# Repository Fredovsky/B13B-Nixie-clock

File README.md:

# B13B-Nixie-clock
Nixie clock made from F9057 Nixie tubes (B13B sockets).

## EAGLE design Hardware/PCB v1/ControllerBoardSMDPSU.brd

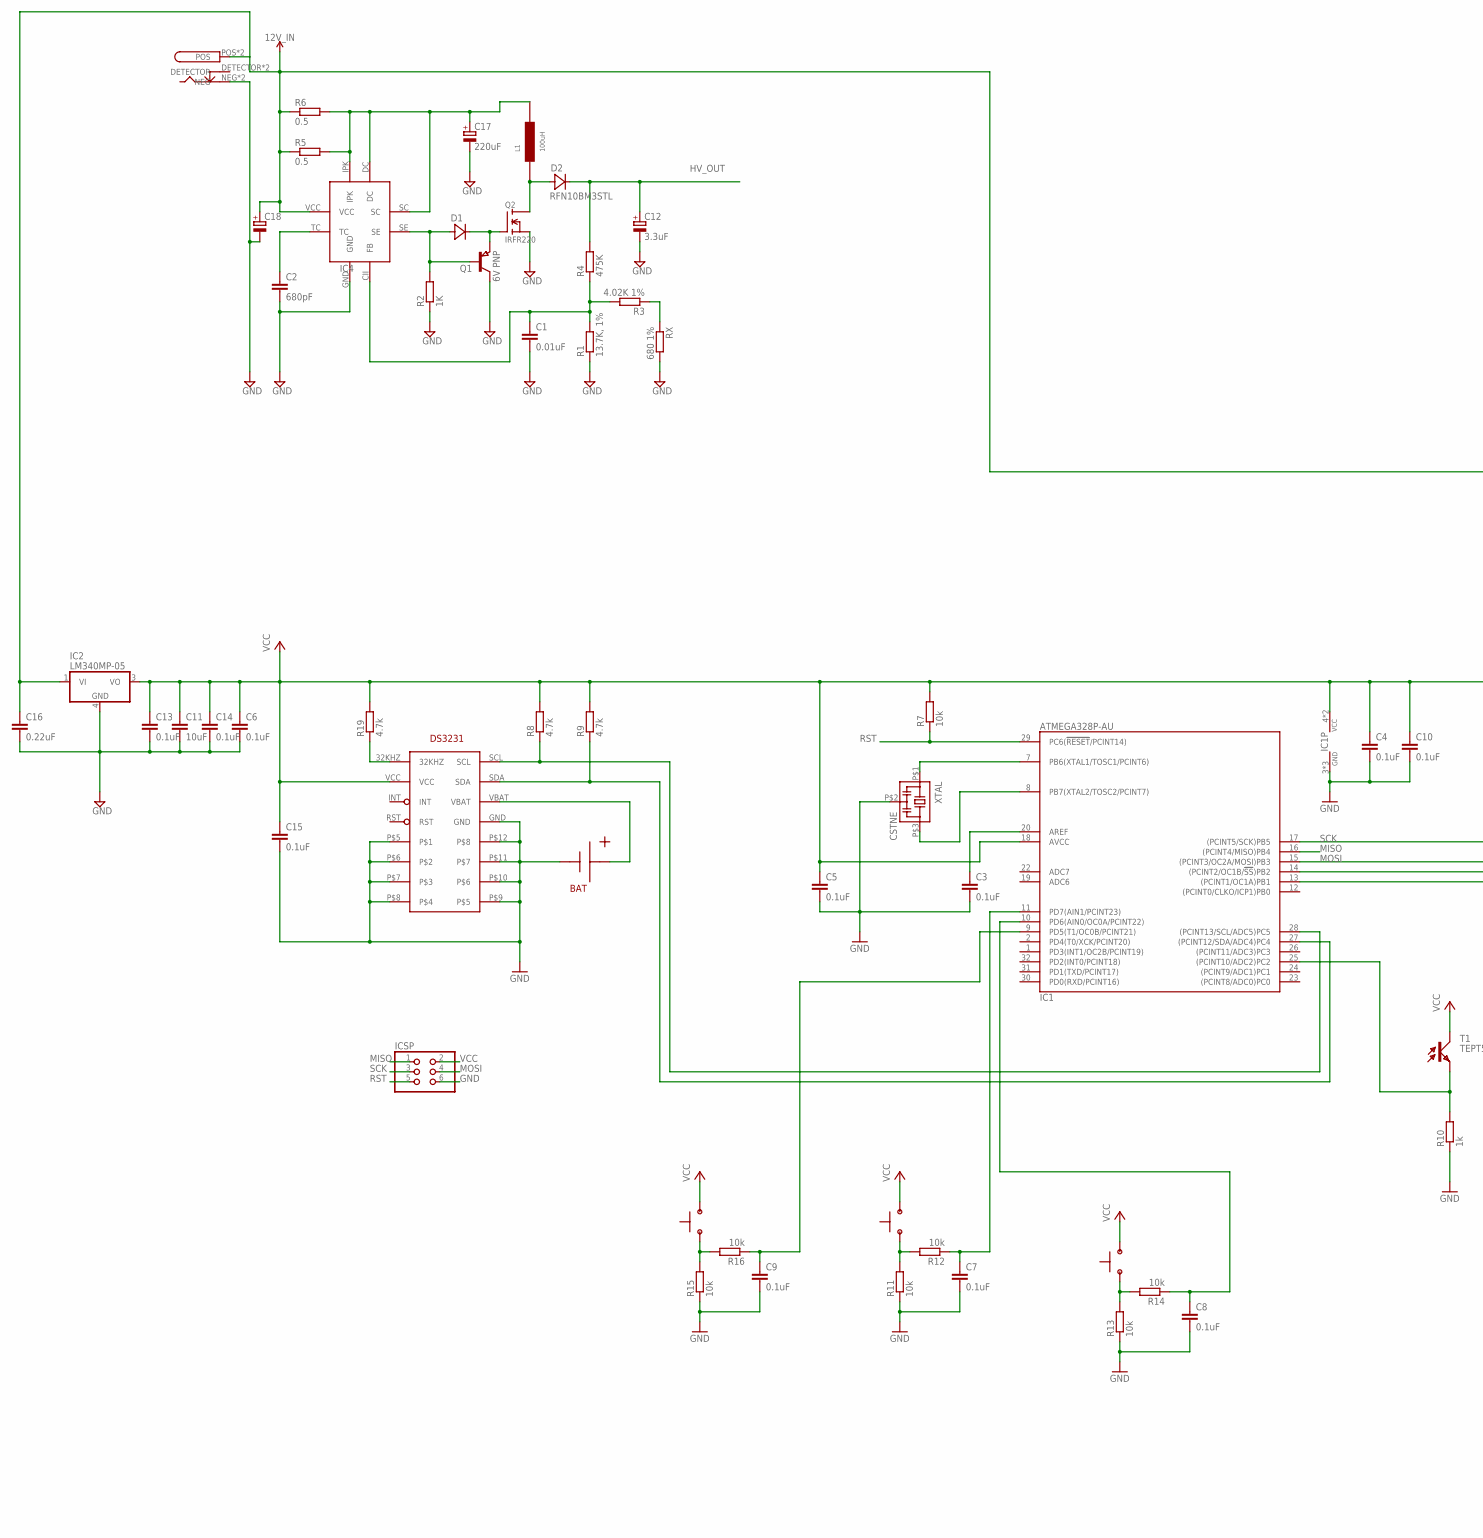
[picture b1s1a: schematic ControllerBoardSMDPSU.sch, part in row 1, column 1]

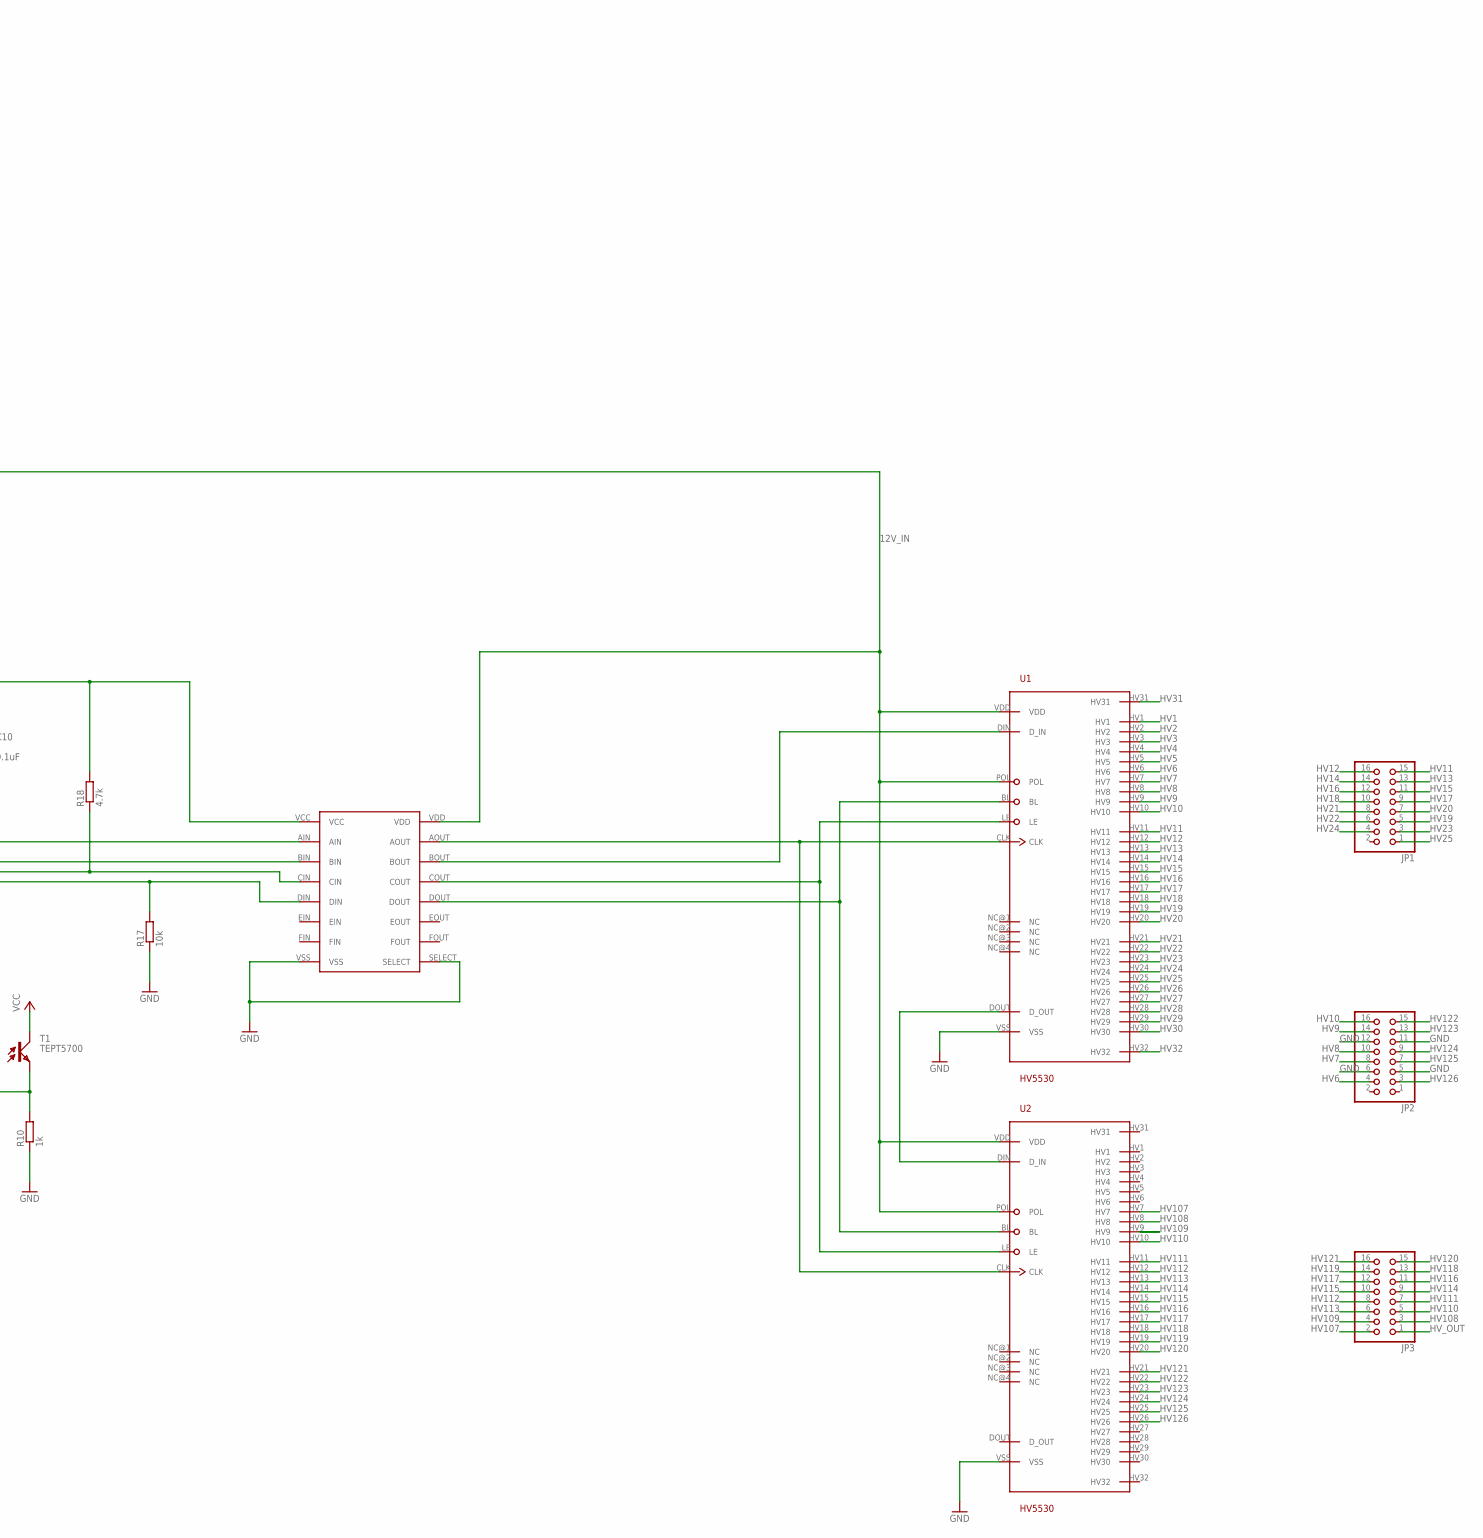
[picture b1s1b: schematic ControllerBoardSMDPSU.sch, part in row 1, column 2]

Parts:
12V: CUI_PWR_JACK
BAT: CR2032-SMD-HLDR; CR2032-SMD
C1: 0.01uF; C0603
C2: 680pF; C0603
C3, C4, C5, C6, C7, C8, C9, C10, C13, C14, C15: 0.1uF; C0603
C11: 10uF; C0603
C12: 3.3uF; 153CLV-0810
C16: 0.22uF; C0603
C17: 220uF; 153CLV-0605
C18: CPOL-EU153CLV-0605; 153CLV-0605
D1: SOT123DIODE; SOD123
D2: RFN10BM3STL; TO252
IC1: ATMEGA328P-AU; QFP32_7X7_0.80
IC2: LM340MP-05; SOT223
IC3: CD4504BTSSOP16; SOP65P640X120-16N
IC4: MC34063; SOIC127P600X175-8
ICSP: PINHD-2X3; 2X03
JP1, JP2, JP3: PINHD-2X8; 2X08
L1: 100uH; SDR1105
Q1: 6V PNP; SOT23
Q2: IRFR220; DPAK
R1: 13.7K, 1%; R1206
R2: 1K; R1206
R3: 4.02K 1%; R1206
R4: 475K; R1206
R5, R6: 0.5; R1206
R7, R11, R12, R13, R14, R15, R16, R17: 10k; R0603
R8, R9, R18, R19: 4.7k; R0603
R10: 1k; R0603
RTC: DS3231-CORRECT; SOIC16-CORRECT
RX: 680 1%; R1206
S1, S2, S3: TL1105
T1: TEPT5700; BPX81
U1, U2: HV5530; 44_PQFP_CORRECTED
XTAL: CSTNE

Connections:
12V_IN: 12V.POS, 12V.POS1 (POS), C16.1, C18.+, IC2.1 (VI), IC3.VDD, IC4.VCC, R5.1, R6.1, U1.POL, U1.VDD, U2.POL, U2.VDD
GND: 12V.NEG, 12V.NEG1 (NEG), BAT.NEG, C1.2, C2.2, C3.2, C4.2, C5.2, C6.2, C7.2, C8.2, C9.2, C10.2, C11.2, C12.-, C13.2, C14.2, C15.2, C16.2, C17.-, C18.-, IC1.3 (GND), IC1.5 (GND), IC1.21 (GND), IC2.4 (GND), IC3.SELECT, IC3.VSS, IC4.GND, ICSP.6, JP2.5, JP2.6, JP2.11, JP2.12, Q1.3 (C), Q2.3 (S), R1.1, R2.1, R10.1, R11.1, R13.1, R15.1, R17.1, RTC.GND, RTC.P$5, RTC.P$6, RTC.P$7, RTC.P$8, RTC.P$9, RTC.P$10, RTC.P$11, RTC.P$12, RX.2, U1.VSS, U2.VSS, XTAL.P$2 (2)
HV1: U1.HV1
HV2: U1.HV2
HV3: U1.HV3
HV4: U1.HV4
HV5: U1.HV5
HV6: JP2.4, U1.HV6
HV7: JP2.8, U1.HV7
HV8: JP2.10, U1.HV8
HV9: JP2.14, U1.HV9
HV10: JP2.16, U1.HV10
HV11: JP1.15, U1.HV11
HV12: JP1.16, U1.HV12
HV13: JP1.13, U1.HV13
HV14: JP1.14, U1.HV14
HV15: JP1.11, U1.HV15
HV16: JP1.12, U1.HV16
HV17: JP1.9, U1.HV17
HV18: JP1.10, U1.HV18
HV19: JP1.5, U1.HV19
HV20: JP1.7, U1.HV20
HV21: JP1.8, U1.HV21
HV22: JP1.6, U1.HV22
HV23: JP1.3, U1.HV23
HV24: JP1.4, U1.HV24
HV25: JP1.1, U1.HV25
HV26: U1.HV26
HV27: U1.HV27
HV28: U1.HV28
HV29: U1.HV29
HV30: U1.HV30
HV31: U1.HV31
HV32: U1.HV32
HV107: JP3.2, U2.HV7
HV108: JP3.3, U2.HV8
HV109: JP3.4, U2.HV9
HV110: JP3.5, U2.HV10
HV111: JP3.7, U2.HV11
HV112: JP3.8, U2.HV12
HV113: JP3.6, U2.HV13
HV114: JP3.9, U2.HV14
HV115: JP3.10, U2.HV15
HV116: JP3.11, U2.HV16
HV117: JP3.12, U2.HV17
HV118: JP3.13, U2.HV18
HV119: JP3.14, U2.HV19
HV120: JP3.15, U2.HV20
HV121: JP3.16, U2.HV21
HV122: JP2.15, U2.HV22
HV123: JP2.13, U2.HV23
HV124: JP2.9, U2.HV24
HV125: JP2.7, U2.HV25
HV126: JP2.3, U2.HV26
HV_OUT: C12.+, D2.3 (C), JP3.1, R4.2
MISO: IC1.16 ((PCINT4/MISO)PB4), ICSP.1
MOSI: IC1.15 ((PCINT3/OC2A/MOSI)PB3), IC3.BIN, ICSP.4
unnamed: BAT.POS@1 (POS), BAT.POS@2 (POS), RTC.VBAT
unnamed: IC1.7 (PB6(XTAL1/TOSC1/PCINT6)), XTAL.P$1 (1)
unnamed: IC1.8 (PB7(XTAL2/TOSC2/PCINT7)), XTAL.P$3 (3)
unnamed: R19.1, RTC.32KHZ
unnamed: IC3.AOUT, U1.CLK, U2.CLK
unnamed: U1.DOUT (D_OUT), U2.DIN (D_IN)
unnamed: IC3.BOUT, U1.DIN (D_IN)
unnamed: C17.+, IC4.DC, IC4.IPK, IC4.SC, L1.P$2, R5.2, R6.2
unnamed: C2.1, IC4.TC
unnamed: D1.2 (A), IC4.SE, Q1.1 (B), R2.2
unnamed: D1.1 (C), Q1.2 (E), Q2.1 (G)
unnamed: D2.1 (A), D2.2 (A), L1.P$1, Q2.2 (D)
unnamed: C1.1, IC4.CII (FB), R1.2, R3.2, R4.1
unnamed: IC1.14 ((PCINT2/OC1B/!SS!)PB2), IC3.CIN, R18.1
unnamed: IC1.13 ((PCINT1/OC1A)PB1), IC3.DIN, R17.2
unnamed: IC3.COUT, U1.LE, U2.LE
unnamed: IC3.DOUT, U1.BL, U2.BL
unnamed: C3.1, IC1.20 (AREF)
unnamed: IC1.25 ((PCINT10/ADC2)PC2), R10.2, T1.E
unnamed: R3.1, RX.1
unnamed: R13.2, R14.2, S2.1, S2.2
unnamed: R11.2, R12.2, S1.1, S1.2
unnamed: C8.1, IC1.10 (PD6(AIN0/OC0A/PCINT22)), R14.1
unnamed: C7.1, IC1.11 (PD7(AIN1/PCINT23)), R12.1
unnamed: R15.2, R16.2, S3.1, S3.2
unnamed: C9.1, IC1.9 (PD5(T1/OC0B/PCINT21)), R16.1
RST: IC1.29 (PC6(!RESET!/PCINT14)), ICSP.5, R7.1
SCK: IC1.17 ((PCINT5/SCK)PB5), IC3.AIN, ICSP.3
SCL: IC1.28 ((PCINT13/SCL/ADC5)PC5), R8.1, RTC.SCL
SDA: IC1.27 ((PCINT12/SDA/ADC4)PC4), R9.1, RTC.SDA
VCC: C4.1, C5.1, C6.1, C10.1, C11.1, C13.1, C14.1, C15.1, IC1.4 (VCC), IC1.6 (VCC), IC1.18 (AVCC), IC2.3 (VO), IC3.VCC, ICSP.2, R7.2, R8.2, R9.2, R18.2, R19.2, RTC.VCC, S1.3, S1.4, S2.3, S2.4, S3.3, S3.4, T1.C

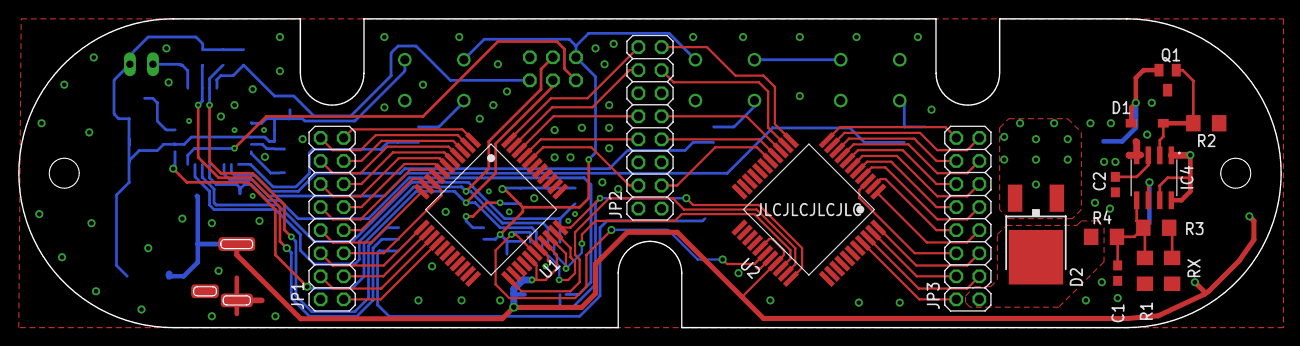
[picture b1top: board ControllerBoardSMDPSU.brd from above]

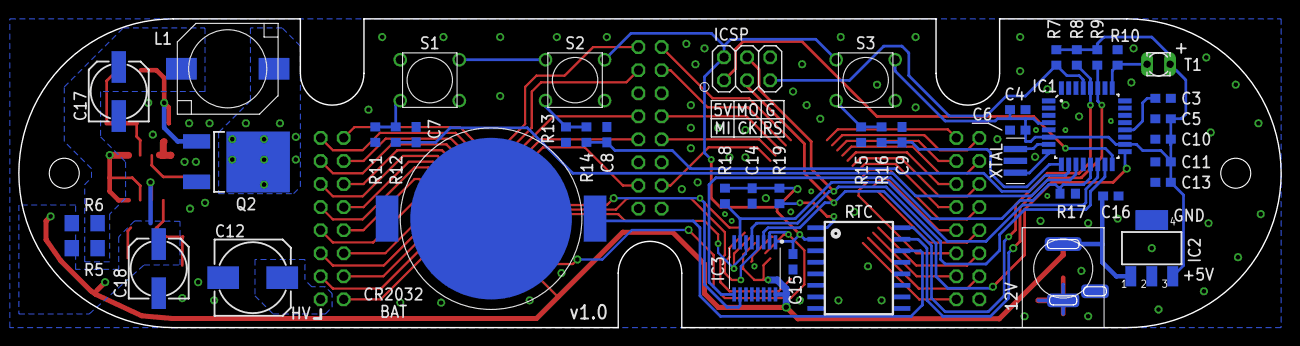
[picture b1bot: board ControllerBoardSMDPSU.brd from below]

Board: 2 copper layers, 139.0 x 34.0 mm, 61 parts (45 on the bottom side), 76 nets.

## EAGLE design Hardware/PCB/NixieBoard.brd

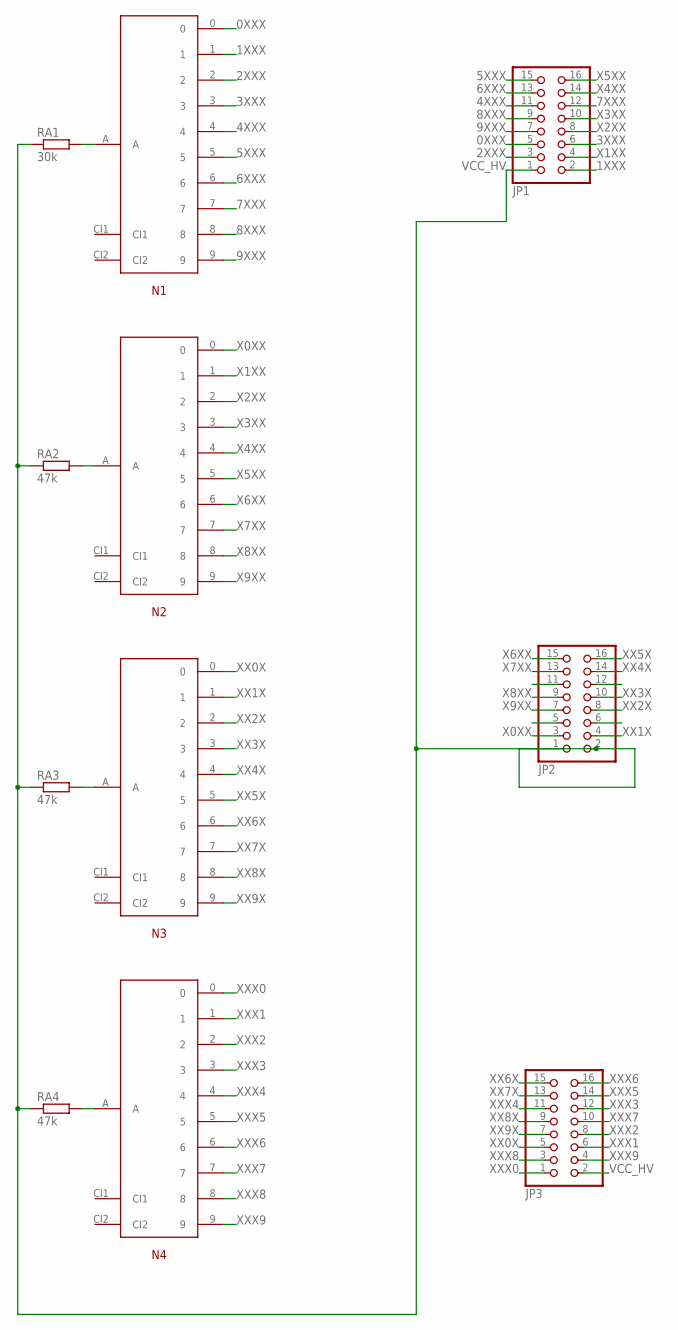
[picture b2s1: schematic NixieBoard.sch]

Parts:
JP1, JP2, JP3: PINHD-2X8; 2X08
N1, N2, N3, N4: F9057TUBE; F9057PIN
RA1: 30k; R2010
RA2, RA3, RA4: 47k; R2010

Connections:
0XXX: JP1.5, N1.0
1XXX: JP1.2, N1.1
2XXX: JP1.3, N1.2
3XXX: JP1.6, N1.3
4XXX: JP1.11, N1.4
5XXX: JP1.15, N1.5
6XXX: JP1.13, N1.6
7XXX: JP1.12, N1.7
8XXX: JP1.9, N1.8
9XXX: JP1.7, N1.9
unnamed: N4.A, RA4.2
unnamed: N3.A, RA3.2
unnamed: N2.A, RA2.2
unnamed: N1.A, RA1.2
VCC_HV: JP1.1, JP2.1, JP2.2, JP3.2, RA1.1, RA2.1, RA3.1, RA4.1
X0XX: JP2.3, N2.0
X1XX: JP1.4, N2.1
X2XX: JP1.8, N2.2
X3XX: JP1.10, N2.3
X4XX: JP1.14, N2.4
X5XX: JP1.16, N2.5
X6XX: JP2.15, N2.6
X7XX: JP2.13, N2.7
X8XX: JP2.9, N2.8
X9XX: JP2.7, N2.9
XX0X: JP3.5, N3.0
XX1X: JP2.4, N3.1
XX2X: JP2.8, N3.2
XX3X: JP2.10, N3.3
XX4X: JP2.14, N3.4
XX5X: JP2.16, N3.5
XX6X: JP3.15, N3.6
XX7X: JP3.13, N3.7
XX8X: JP3.9, N3.8
XX9X: JP3.7, N3.9
XXX0: JP3.1, N4.0
XXX1: JP3.6, N4.1
XXX2: JP3.8, N4.2
XXX3: JP3.12, N4.3
XXX4: JP3.11, N4.4
XXX5: JP3.14, N4.5
XXX6: JP3.16, N4.6
XXX7: JP3.10, N4.7
XXX8: JP3.3, N4.8
XXX9: JP3.4, N4.9

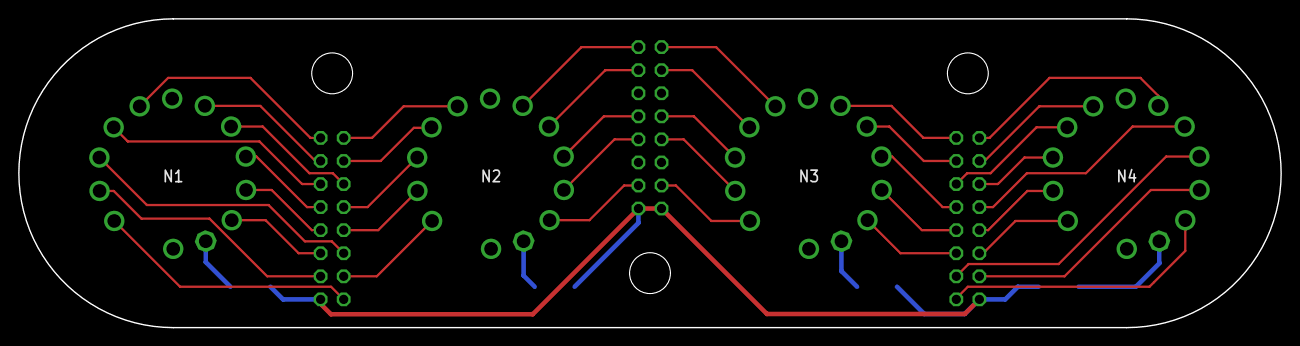
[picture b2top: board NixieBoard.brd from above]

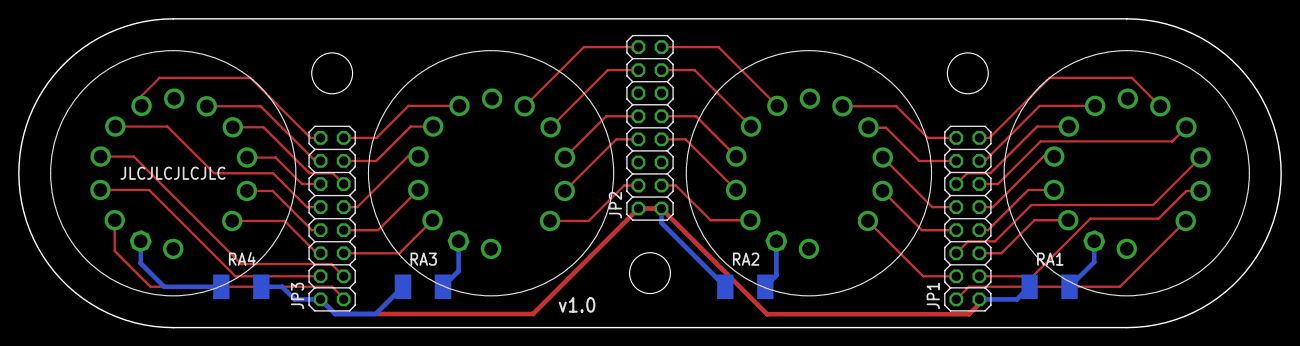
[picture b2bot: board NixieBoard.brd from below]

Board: 2 copper layers, 139.0 x 34.0 mm, 11 parts (7 on the bottom side), 45 nets.

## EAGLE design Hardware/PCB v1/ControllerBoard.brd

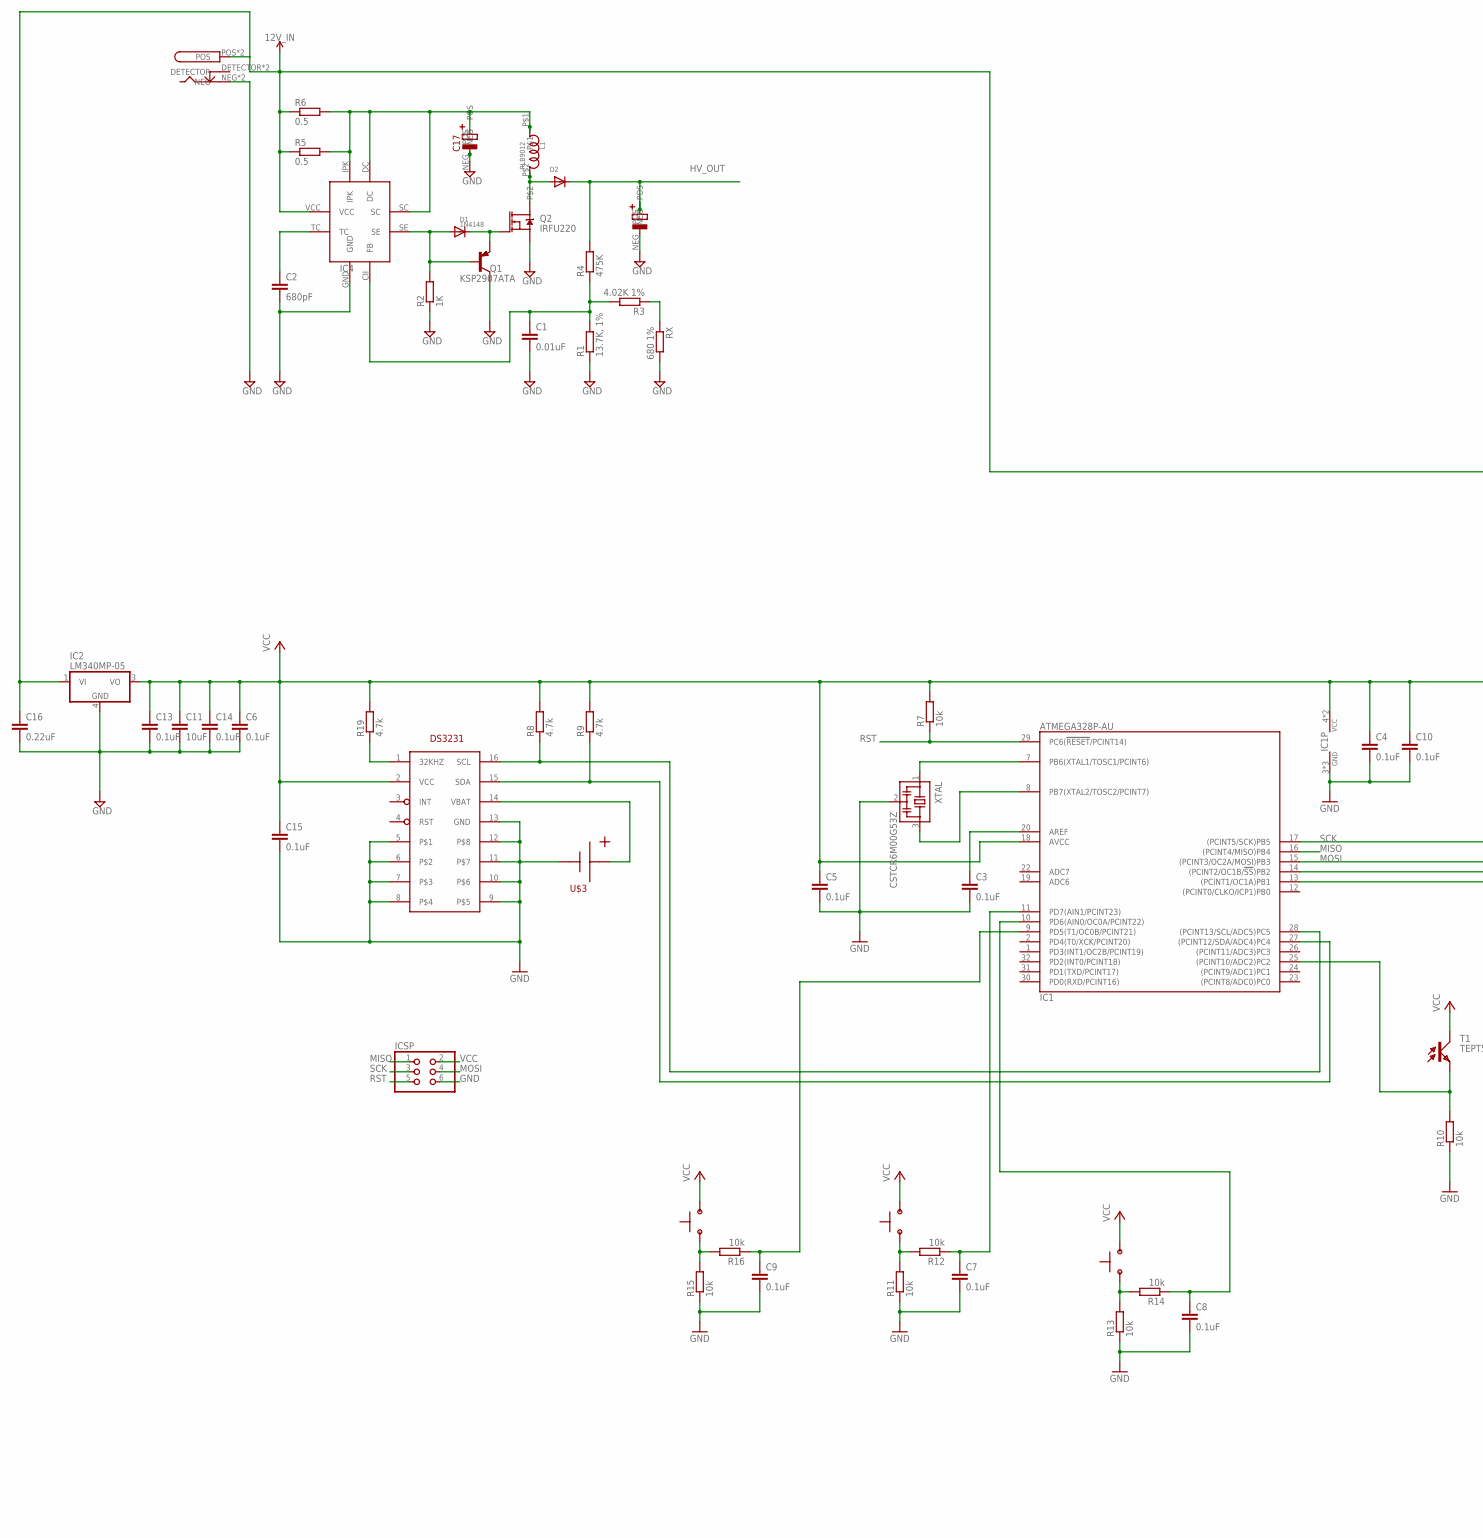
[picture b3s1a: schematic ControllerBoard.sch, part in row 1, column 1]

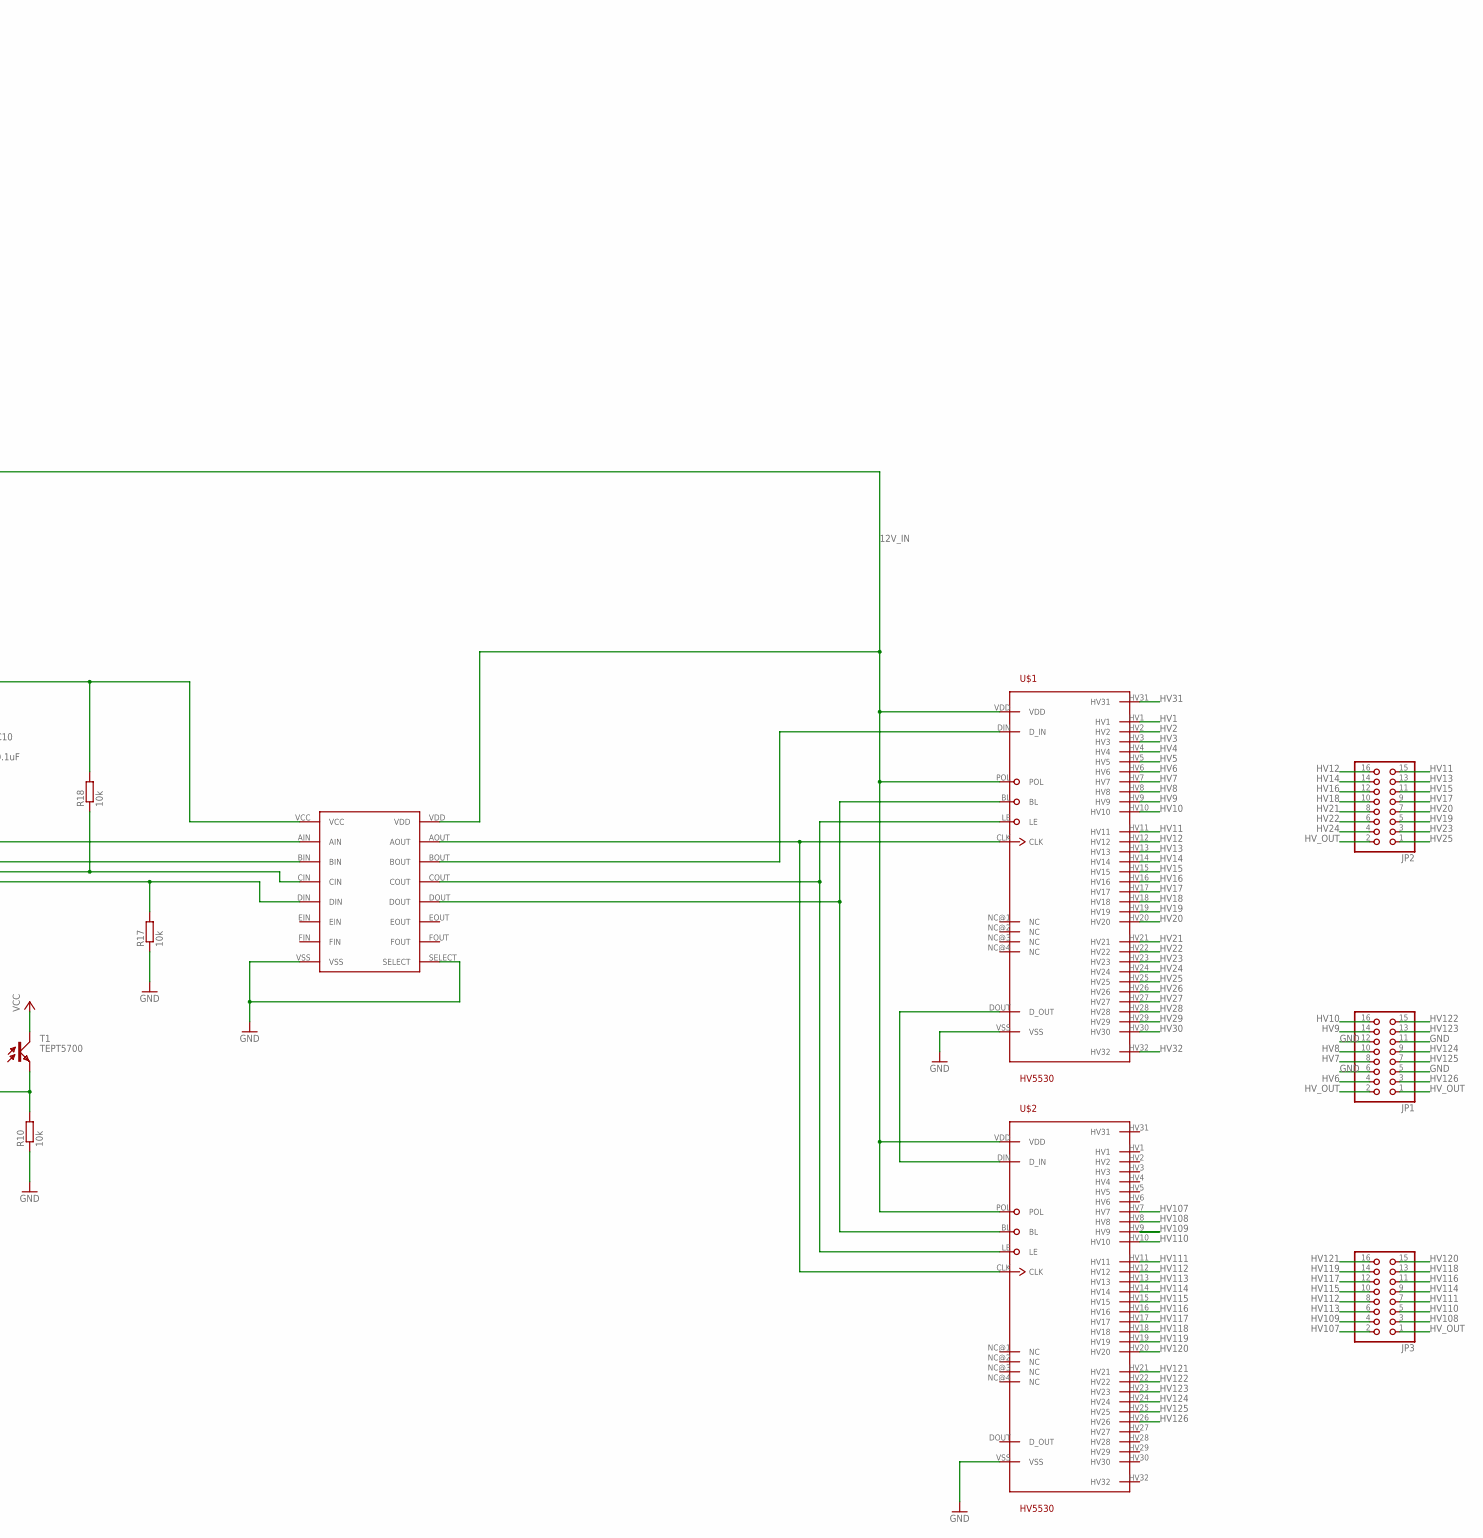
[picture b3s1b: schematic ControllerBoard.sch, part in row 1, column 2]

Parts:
12V: CUI_PWR_JACK
C1: 0.01uF; C0603
C2: 680pF; C0603
C3, C4, C5, C6, C7, C8, C9, C10, C13, C14, C15: 0.1uF; C0603
C11: 10uF; C0603
C12: ECA-2DM3R3
C16: 0.22uF; C0603
C17: EEU-FM1
D1: 1N4148; SOD-123
D2: DIODESOD-123; SOD-123
IC1: ATMEGA328P-AU; QFP32_7X7_0.80
IC2: LM340MP-05; SOT223
IC3: CD4504BTSSOP16; SOP65P640X120-16N
IC4: MC34063; SOIC127P600X175-8
ICSP: PINHD-2X3; 2X03
JP1, JP2, JP3: PINHD-2X8; 2X08
L1: RLB9012
Q1: KSP2907ATA; TO92-EBC-OVAL
Q2: IRFU220; TO220V
R1: 13.7K, 1%; R1206
R2: 1K; R1206
R3: 4.02K 1%; R1206
R4: 475K; R1206
R5, R6: 0.5; R1206
R7, R10, R11, R12, R13, R14, R15, R16, R17, R18: 10k; R0603
R8, R9, R19: 4.7k; R0603
RTC: DS3231; SO16
RX: 680 1%; R1206
S1, S2, S3: TL1105
T1: TEPT5700; BPX81
U$1, U$2: HV5530; 44_PQFP_CORRECTED
U$3: CR2032-SMD-HLDR; CR2032-SMD
XTAL: CSTCR6M00G53Z; CSTCR6M

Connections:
12V_IN: 12V.POS, 12V.POS1 (POS), C16.1, IC2.1 (VI), IC3.VDD, IC4.VCC, R5.1, R6.1, U$1.POL, U$1.VDD, U$2.POL, U$2.VDD
GND: 12V.NEG, 12V.NEG1 (NEG), C1.2, C2.2, C3.2, C4.2, C5.2, C6.2, C7.2, C8.2, C9.2, C10.2, C11.2, C12.NEG, C13.2, C14.2, C15.2, C16.2, C17.NEG, IC1.3 (GND), IC1.5 (GND), IC1.21 (GND), IC2.4 (GND), IC3.SELECT, IC3.VSS, IC4.GND, ICSP.6, JP1.5, JP1.6, JP1.11, JP1.12, Q1.C, Q2.3 (S), R1.1, R2.1, R10.1, R11.1, R13.1, R15.1, R17.1, RTC.5, RTC.6, RTC.7, RTC.8, RTC.9, RTC.10, RTC.11, RTC.12, RTC.13 (GND), RX.2, U$1.VSS, U$2.VSS, U$3.NEG, XTAL.2
HV1: U$1.HV1
HV2: U$1.HV2
HV3: U$1.HV3
HV4: U$1.HV4
HV5: U$1.HV5
HV6: JP1.4, U$1.HV6
HV7: JP1.8, U$1.HV7
HV8: JP1.10, U$1.HV8
HV9: JP1.14, U$1.HV9
HV10: JP1.16, U$1.HV10
HV11: JP2.15, U$1.HV11
HV12: JP2.16, U$1.HV12
HV13: JP2.13, U$1.HV13
HV14: JP2.14, U$1.HV14
HV15: JP2.11, U$1.HV15
HV16: JP2.12, U$1.HV16
HV17: JP2.9, U$1.HV17
HV18: JP2.10, U$1.HV18
HV19: JP2.5, U$1.HV19
HV20: JP2.7, U$1.HV20
HV21: JP2.8, U$1.HV21
HV22: JP2.6, U$1.HV22
HV23: JP2.3, U$1.HV23
HV24: JP2.4, U$1.HV24
HV25: JP2.1, U$1.HV25
HV26: U$1.HV26
HV27: U$1.HV27
HV28: U$1.HV28
HV29: U$1.HV29
HV30: U$1.HV30
HV31: U$1.HV31
HV32: U$1.HV32
HV107: JP3.2, U$2.HV7
HV108: JP3.3, U$2.HV8
HV109: JP3.4, U$2.HV9
HV110: JP3.5, U$2.HV10
HV111: JP3.7, U$2.HV11
HV112: JP3.8, U$2.HV12
HV113: JP3.6, U$2.HV13
HV114: JP3.9, U$2.HV14
HV115: JP3.10, U$2.HV15
HV116: JP3.11, U$2.HV16
HV117: JP3.12, U$2.HV17
HV118: JP3.13, U$2.HV18
HV119: JP3.14, U$2.HV19
HV120: JP3.15, U$2.HV20
HV121: JP3.16, U$2.HV21
HV122: JP1.15, U$2.HV22
HV123: JP1.13, U$2.HV23
HV124: JP1.9, U$2.HV24
HV125: JP1.7, U$2.HV25
HV126: JP1.3, U$2.HV26
HV_OUT: C12.POS, D2.C, JP1.1, JP1.2, JP2.2, JP3.1, R4.2
MISO: IC1.16 ((PCINT4/MISO)PB4), ICSP.1
MOSI: IC1.15 ((PCINT3/OC2A/MOSI)PB3), IC3.BIN, ICSP.4
unnamed: RTC.14 (VBAT), U$3.POS@1 (POS), U$3.POS@2 (POS)
unnamed: IC1.7 (PB6(XTAL1/TOSC1/PCINT6)), XTAL.1
unnamed: IC1.8 (PB7(XTAL2/TOSC2/PCINT7)), XTAL.3
unnamed: R19.1, RTC.1 (32KHZ)
unnamed: IC3.AOUT, U$1.CLK, U$2.CLK
unnamed: U$1.DOUT (D_OUT), U$2.DIN (D_IN)
unnamed: IC3.BOUT, U$1.DIN (D_IN)
unnamed: C17.POS, IC4.DC, IC4.IPK, IC4.SC, L1.P$1, R5.2, R6.2
unnamed: C2.1, IC4.TC
unnamed: D1.A, IC4.SE, Q1.B, R2.2
unnamed: D1.C, Q1.E, Q2.1 (G)
unnamed: D2.A, L1.P$2, Q2.2 (D)
unnamed: C1.1, IC4.CII (FB), R1.2, R3.2, R4.1
unnamed: IC1.14 ((PCINT2/OC1B/!SS!)PB2), IC3.CIN, R18.1
unnamed: IC1.13 ((PCINT1/OC1A)PB1), IC3.DIN, R17.2
unnamed: IC3.COUT, U$1.LE, U$2.LE
unnamed: IC3.DOUT, U$1.BL, U$2.BL
unnamed: C3.1, IC1.20 (AREF)
unnamed: IC1.25 ((PCINT10/ADC2)PC2), R10.2, T1.E
unnamed: R3.1, RX.1
unnamed: R13.2, R14.2, S2.1, S2.2
unnamed: R11.2, R12.2, S1.1, S1.2
unnamed: C8.1, IC1.10 (PD6(AIN0/OC0A/PCINT22)), R14.1
unnamed: C7.1, IC1.11 (PD7(AIN1/PCINT23)), R12.1
unnamed: R15.2, R16.2, S3.1, S3.2
unnamed: C9.1, IC1.9 (PD5(T1/OC0B/PCINT21)), R16.1
RST: IC1.29 (PC6(!RESET!/PCINT14)), ICSP.5, R7.1
SCK: IC1.17 ((PCINT5/SCK)PB5), IC3.AIN, ICSP.3
SCL: IC1.28 ((PCINT13/SCL/ADC5)PC5), R8.1, RTC.16 (SCL)
SDA: IC1.27 ((PCINT12/SDA/ADC4)PC4), R9.1, RTC.15 (SDA)
VCC: C4.1, C5.1, C6.1, C10.1, C11.1, C13.1, C14.1, C15.1, IC1.4 (VCC), IC1.6 (VCC), IC1.18 (AVCC), IC2.3 (VO), IC3.VCC, ICSP.2, R7.2, R8.2, R9.2, R18.2, R19.2, RTC.2 (VCC), S1.3, S1.4, S2.3, S2.4, S3.3, S3.4, T1.C

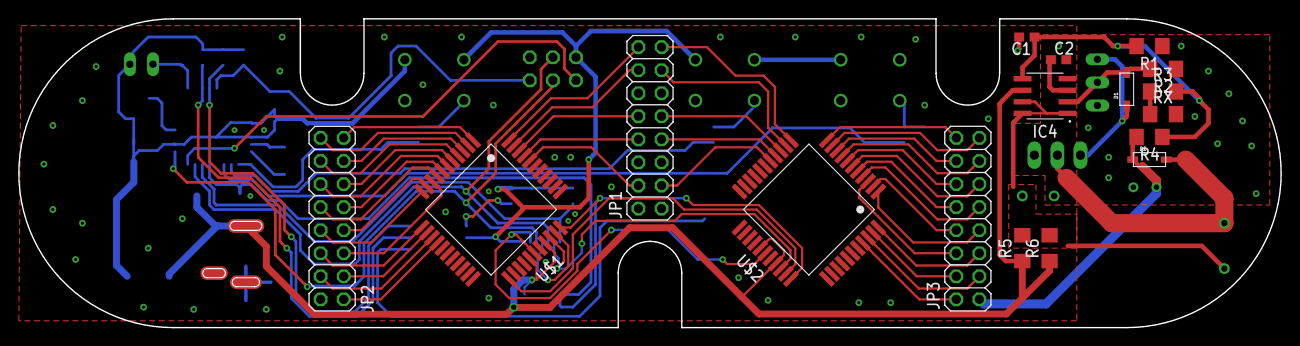
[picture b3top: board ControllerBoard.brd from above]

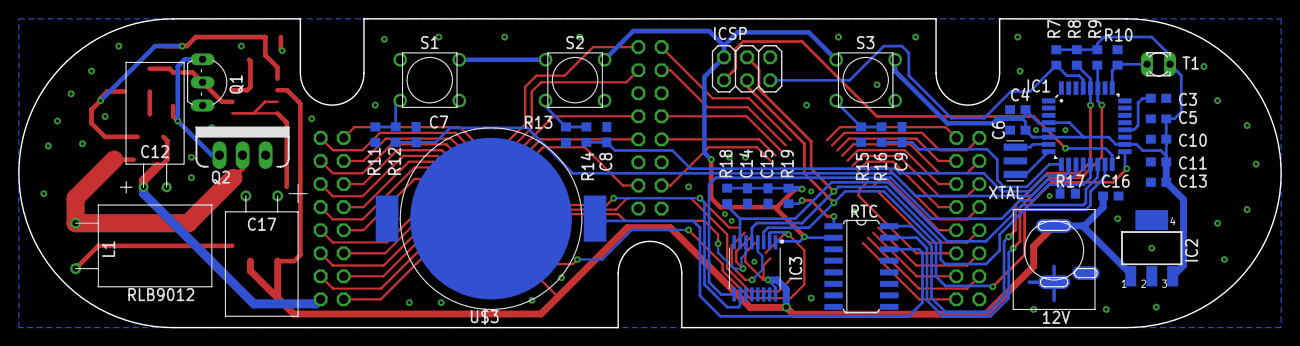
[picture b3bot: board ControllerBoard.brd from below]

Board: 2 copper layers, 139.0 x 34.0 mm, 60 parts (43 on the bottom side), 76 nets.

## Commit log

2021-03-23 Project creation
    Added all project files.
2021-03-23 Reorganized files and added PCB BOM.
    Bill of materials added for V1 of the clock PCB using SMD for PSU.
2021-12-12 First flash CPU clock bug fix
    RTCLib version added and CPU clock speed protocol for first upload.
2021-12-23 Update main.cpp
    Long Cathode Poisoning Prevention Routine set for 30min at 3am, short routine every hour for 15 seconds.
2025-10-16 Added v1.1
    v1.1 = modified Control board and back board for simpler 2-buttons set up (no more date/year functionnality as it was useless).
    PCBs now all on KiCAD.
    Added an updated BOM and 3D Print files if unable to make wooden case.
2025-12-12 Set CPU frequency to 16MHz and configure fuses
    Updated CPU frequency to 16MHz and added fuse settings for external crystal.
2025-12-12 Add temporary file to Software directory
2025-12-12 Update README for Nixie Clock v1.1 changes
    V1.1 update removes a push button and light sensor, changes back button functions, and adjusts brightness automatically.
2025-12-12 Update README for Nixie Clock v1.1 features and changes
    Version 1.1 introduces a simplified interface and improved features, including automatic brightness adjustment and error handling.
2025-12-12 Refactor main.cpp for improved readability v1.1
    v1.1 Refactor main.cpp for improved readability and maintainability. Updated button handling, display logic, and constants for better clarity.

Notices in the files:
parts and their libraries:
SparkFun-DiscreteSemi: Licensing: Creative Commons ShareAlike 4.0 International - https://creativecommons.org/licenses/by-sa/4.0
